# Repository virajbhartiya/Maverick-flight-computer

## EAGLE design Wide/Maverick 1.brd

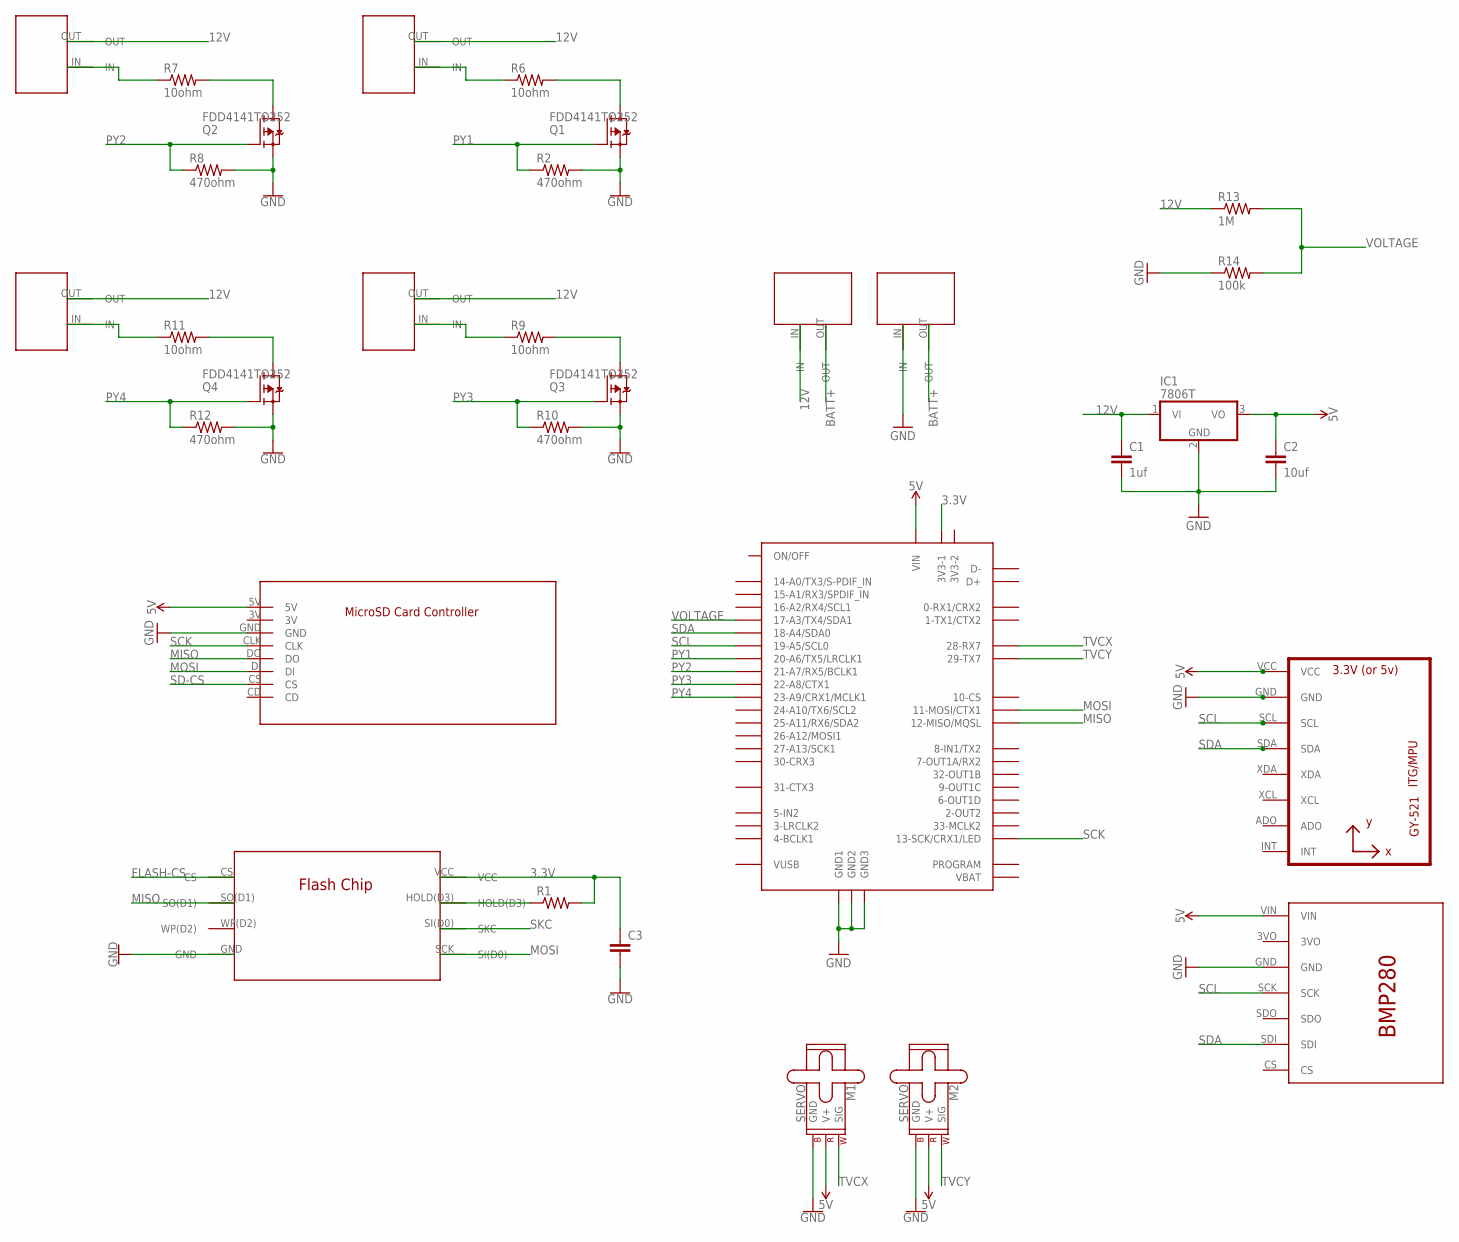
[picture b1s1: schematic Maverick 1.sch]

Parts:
C1: 1uf; C2.5-3
C2: 10uf; C2.5-3
C3: C2,5-3; C2.5-3
IC1: 7806T; TO220H
M1, M2: SERVO; 1X03
Q1, Q2, Q3, Q4: FDD4141TO252; TO252
R1: R-US_0411/3V; 0411V
R2, R8, R10, R12: 470ohm; 0411/15
R6, R7, R9, R11: 10ohm; 0411V
R13: 1M; 0411/15
R14: 100k; 0411/15
U4: GY-521MPU6050; GY-521
U$1: TEENSY40
U$2: BMP280
U$3: SDCARDHOLDER
U$4: FLASHCHIP
U$6, U$7, U$8, U$9, U$10, U$11: TERMBLOCK

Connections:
3.3V: C3.1, R1.2, U$1.3V3-1, U$4.VCC
5V: C2.1, IC1.3 (VO), M1.2 (V+), M2.2 (V+), U4.VCC, U$1.VIN, U$2.VIN, U$3.5V
12V: C1.1, IC1.1 (VI), R13.1, U$6.OUT, U$7.OUT, U$8.OUT, U$9.OUT, U$11.IN
BATT+: U$10.OUT, U$11.OUT
FLASH-CS: U$4.CS
GND: C1.2, C2.2, C3.2, IC1.2 (GND), M1.3 (GND), M2.3 (GND), Q1.2 (S), Q2.2 (S), Q3.2 (S), Q4.2 (S), R2.2, R8.2, R10.2, R12.2, R14.1, U4.GND, U$1.GND1, U$1.GND2, U$1.GND3, U$2.GND, U$3.GND, U$4.GND, U$10.IN
MISO: U$1.12-MIO/MQSL (12-MISO/MQSL), U$3.DO, U$4.SO(D1)
MOSI: U$1.11-MOSI/CTX1, U$3.DI, U$4.SCK (SI(D0))
unnamed: R1.1, U$4.HOLD(D3)
unnamed: Q1.3 (D), R6.2
unnamed: R6.1, U$6.IN
unnamed: R7.1, U$7.IN
unnamed: Q2.3 (D), R7.2
unnamed: R9.1, U$8.IN
unnamed: Q3.3 (D), R9.2
unnamed: R11.1, U$9.IN
unnamed: Q4.3 (D), R11.2
PY1: Q1.1 (G), R2.1, U$1.20-A6/TX5/LRCLK1
PY2: Q2.1 (G), R8.1, U$1.21-A7/RX5/BCLK1
PY3: Q3.1 (G), R10.1, U$1.22-A8/CTX1
PY4: Q4.1 (G), R12.1, U$1.23-A9/CRX1/CCLK1 (23-A9/CRX1/MCLK1)
SCK: U$1.13-SCK/CRX1/LED, U$3.CLK
SCL: U4.SCL, U$1.19-A5/SCL0, U$2.SCK
SD-CS: U$3.CS
SDA: U4.SDA, U$1.18-A4/SDA0, U$2.SDI
SKC: U$4.SI(D0) (SKC)
TVCX: M1.1 (SIG), U$1.28-RX7
TVCY: M2.1 (SIG), U$1.29-TX7
VOLTAGE: R13.2, R14.2, U$1.17-A3/TX4/SDA1

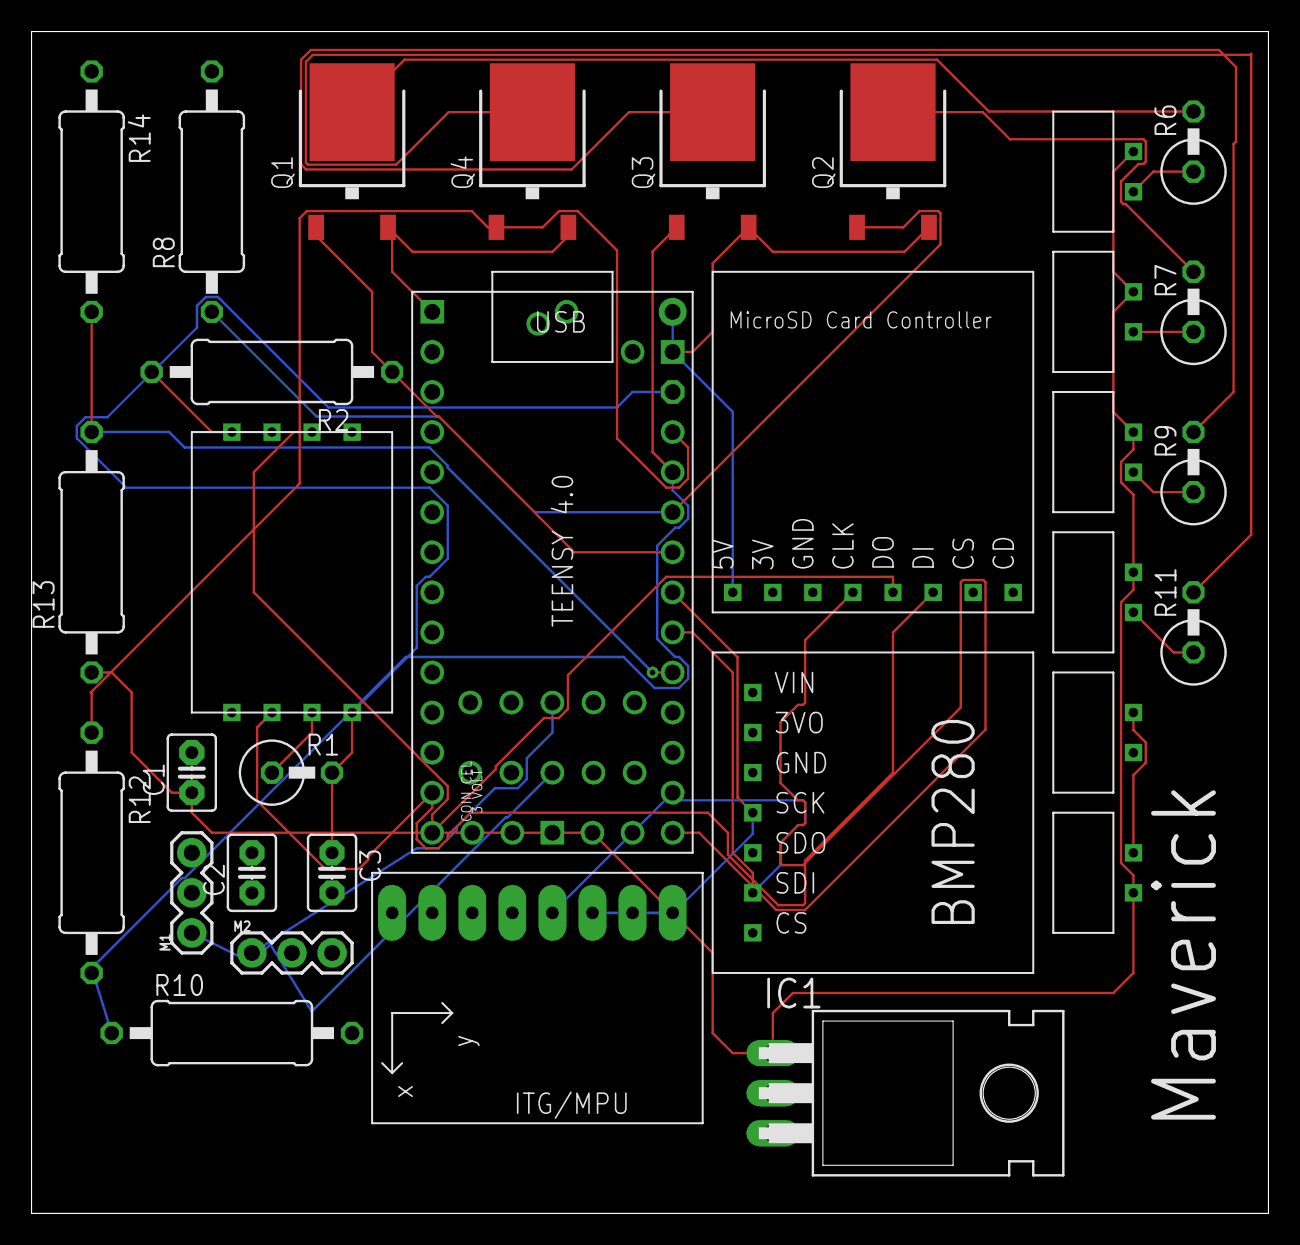
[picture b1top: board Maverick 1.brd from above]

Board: 2 copper layers, 78.4 x 74.9 mm, 32 parts (0 on the bottom side), 26 nets.

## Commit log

2022-09-03 🦅 init0

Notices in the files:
parts and their libraries:
SparkFun-Electromechanical: Licensing: Creative Commons ShareAlike 4.0 International - https://creativecommons.org/licenses/by-sa/4.0
